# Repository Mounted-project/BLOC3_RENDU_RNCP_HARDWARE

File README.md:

# AugMounted-electronics
Electronic repo for the AugMounted line-up

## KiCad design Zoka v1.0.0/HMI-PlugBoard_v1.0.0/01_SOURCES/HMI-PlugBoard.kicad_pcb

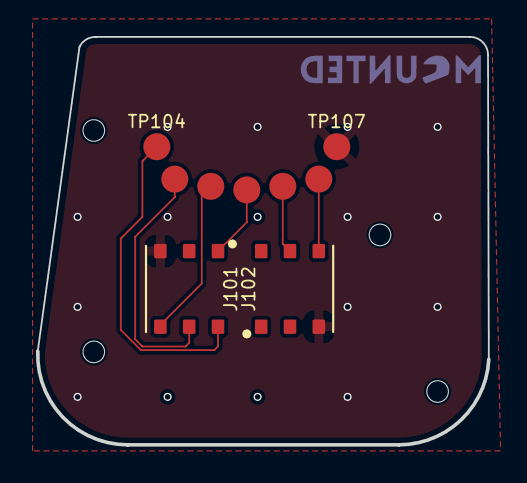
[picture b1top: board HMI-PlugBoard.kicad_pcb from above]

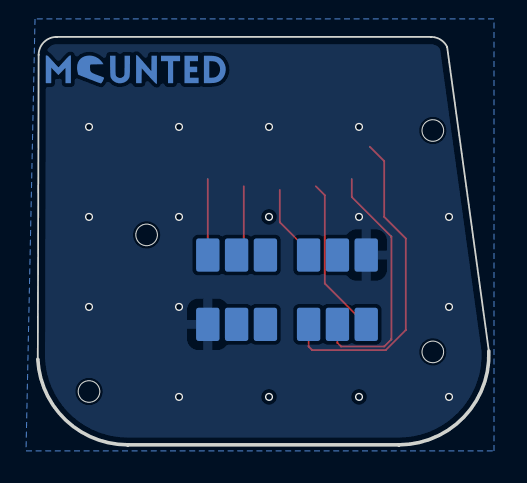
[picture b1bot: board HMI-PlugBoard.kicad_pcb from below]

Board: 2 copper layers, 25.1 x 22.6 mm, 16 parts (3 on the bottom side), 8 nets.

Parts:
H101, H103, H104, H104#2: H_MOUNTING_HOLE_M1; MountingHole_1.2mm_M1
J101, J102: J_0788641001; J_788641001
J101#2, J102#2: J_0788641001_PAD; J_788641001_PAD
LOGO101: mounted_logo
TP101, TP102, TP103, TP104, TP105, TP106, TP107: TESTPOINT_1.5MM

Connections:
/BUTTON1_HMI_BOARD: J101.5, J101#2.5, TP106.1
/BUTTON2_HMI_BOARD: J101.4, J101#2.4, TP105.1
/ENCODER_A_HMI_BOARD: J102.5, J102#2.5, TP101.1
/ENCODER_B_HMI_BOARD: J102.4, J102#2.4, TP102.1
/ENCODER_S1_HMI_BOARD: J102.1, J102#2.1, TP103.1
/ENCODER_S2_HMI_BOARD: J102.6, J102#2.6, TP104.1
GND: J101.3, J101#2.3, J102.3, J102#2.3, TP107.1
VBUS: J102.2, J102#2.2

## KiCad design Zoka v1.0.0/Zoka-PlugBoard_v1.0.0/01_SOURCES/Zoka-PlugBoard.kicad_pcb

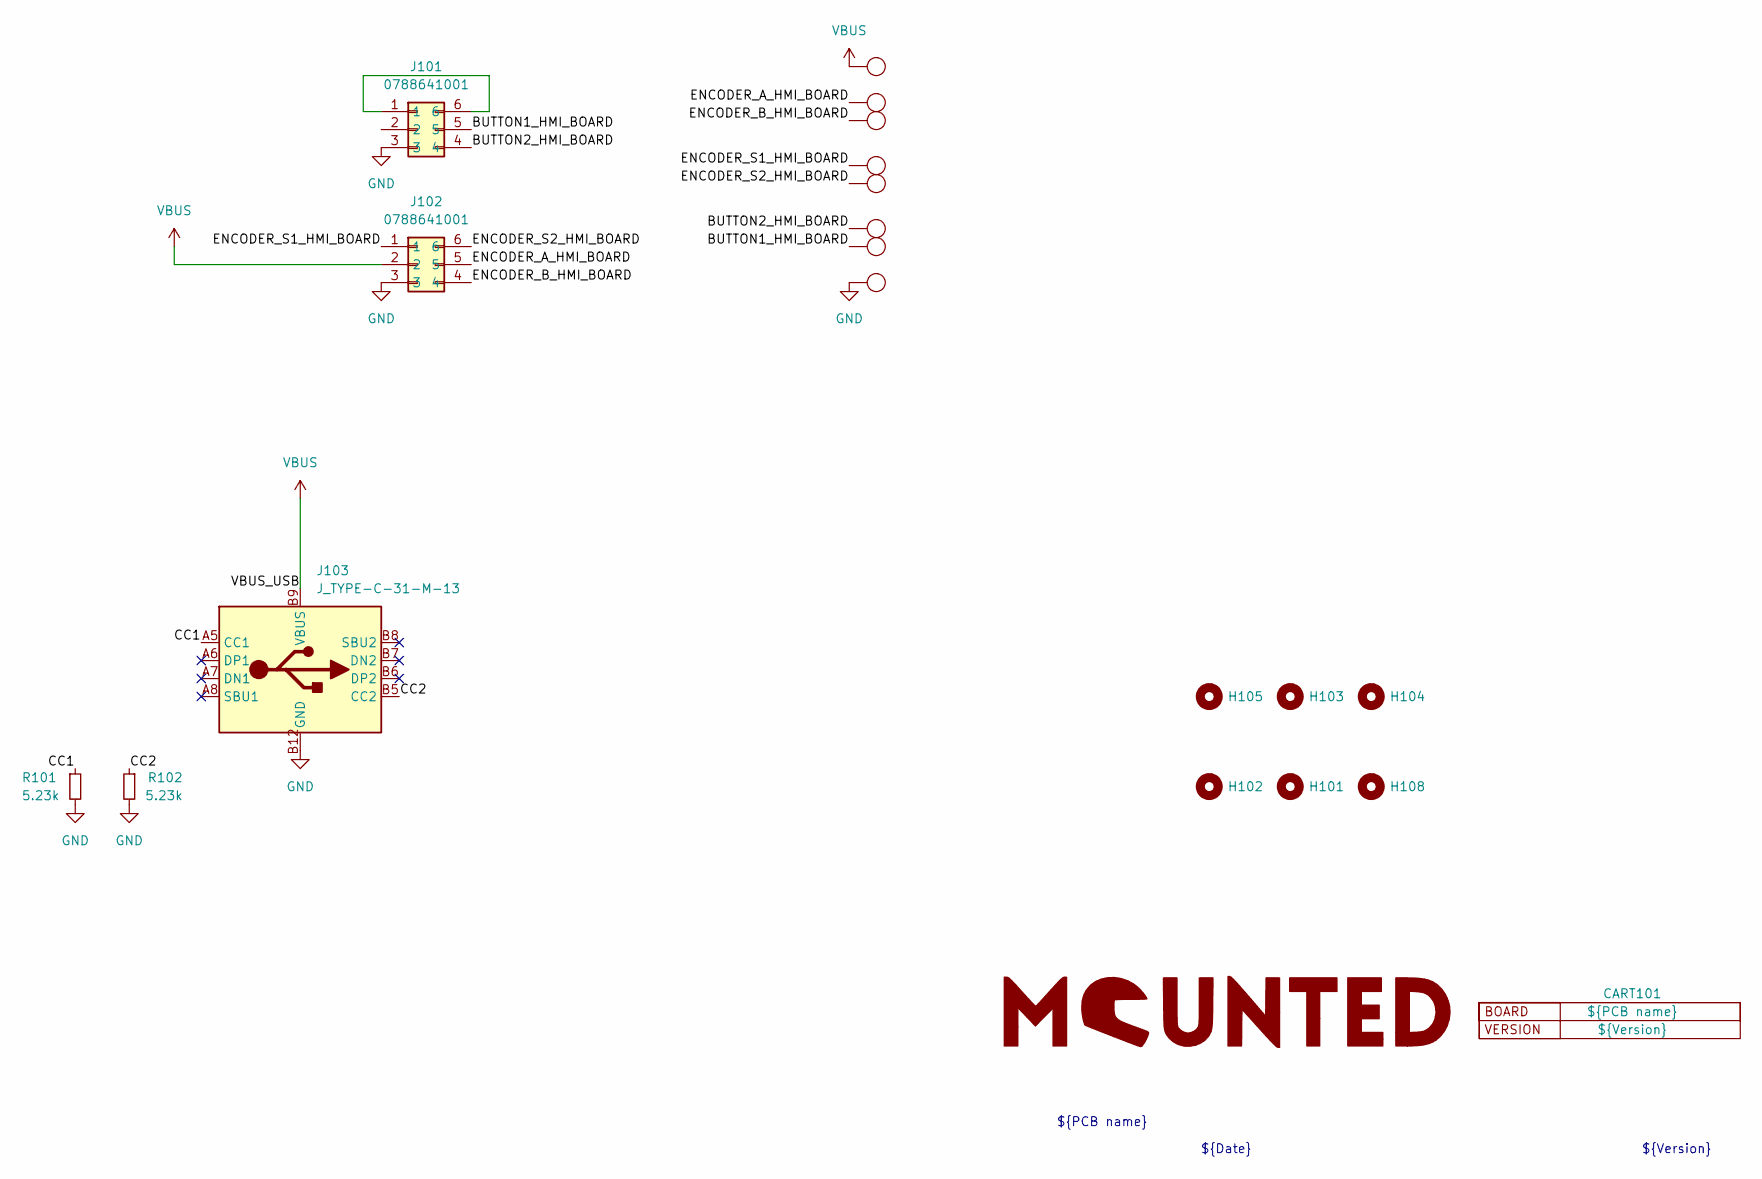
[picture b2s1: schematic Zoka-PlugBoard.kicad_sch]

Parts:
CART101: Cartouche_IO
H101, H102, H103, H104, H105, H108: H_MOUNTING_HOLE_M1; MountingHole_1.2mm_M1
J101, J102: J_0788641001; J_788641001; MPN 0788641001
J103: J_TYPE-C-31-M-13; MPN TYPE-C-31-M-13
LOGO101: mounted_logo
R101, R102: R_0603_5.23k_1%_0.1W; R_0402_1005Metric; Tolerance 1%
TP101, TP102, TP103, TP104, TP105, TP106, TP107, TP108: TESTPOINT_1.5MM

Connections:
/BUTTON1_HMI_BOARD: J101.5, TP106.1
/BUTTON2_HMI_BOARD: J101.4, TP105.1
/CC1: J103.A5 (CC1), R101.1
/CC2: J103.B5 (CC2), R102.1
/ENCODER_A_HMI_BOARD: J102.5, TP101.1
/ENCODER_B_HMI_BOARD: J102.4, TP102.1
/ENCODER_S1_HMI_BOARD: J102.1, TP103.1
/ENCODER_S2_HMI_BOARD: J102.6, TP104.1
GND: J101.3, J102.3, J103.A1 (GND), J103.A12 (GND), J103.B1 (GND), J103.B12 (GND), J103.GND, R101.2, R102.2, TP107.1
unnamed: J101.1, J101.6
VBUS: J102.2, J103.A4 (VBUS), J103.A9 (VBUS), J103.B4 (VBUS), J103.B9 (VBUS), TP108.1

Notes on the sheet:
${PCB name}
${Date}
${Version}

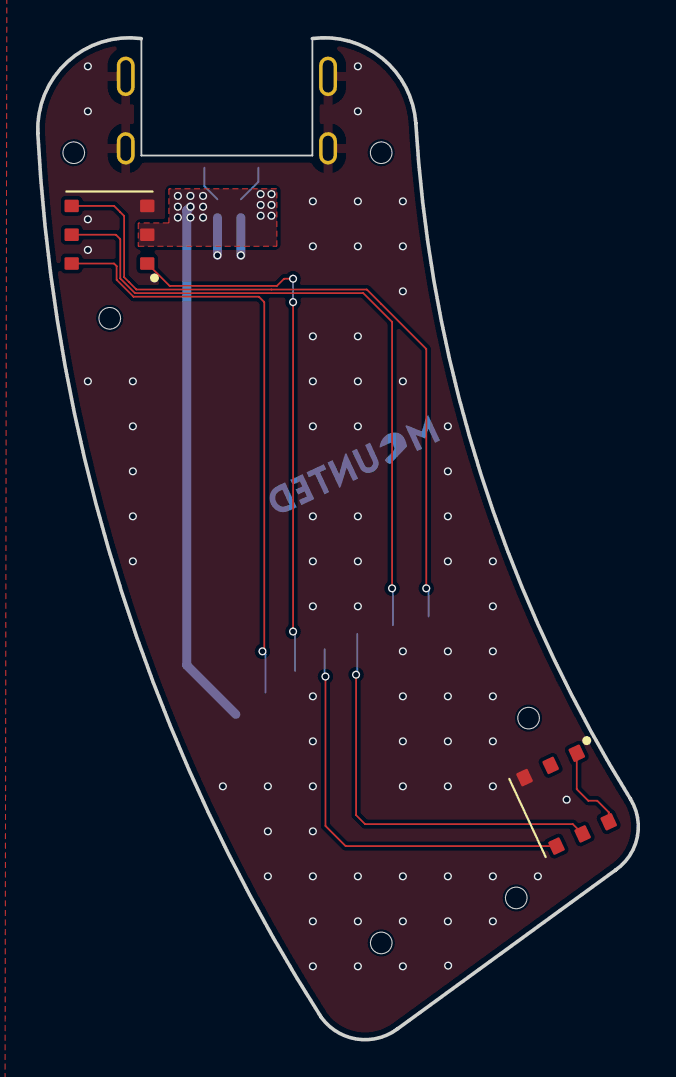
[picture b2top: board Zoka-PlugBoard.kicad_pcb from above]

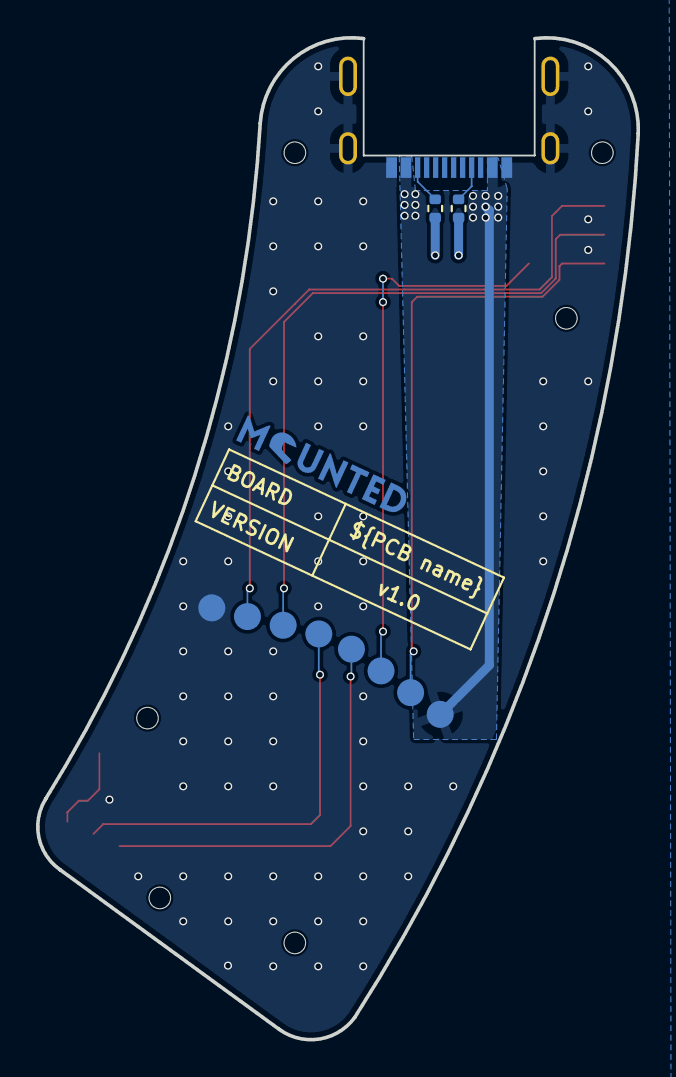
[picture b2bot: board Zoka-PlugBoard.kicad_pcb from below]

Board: 4 copper layers, 33.4 x 55.7 mm, 21 parts (13 on the bottom side), 11 nets.

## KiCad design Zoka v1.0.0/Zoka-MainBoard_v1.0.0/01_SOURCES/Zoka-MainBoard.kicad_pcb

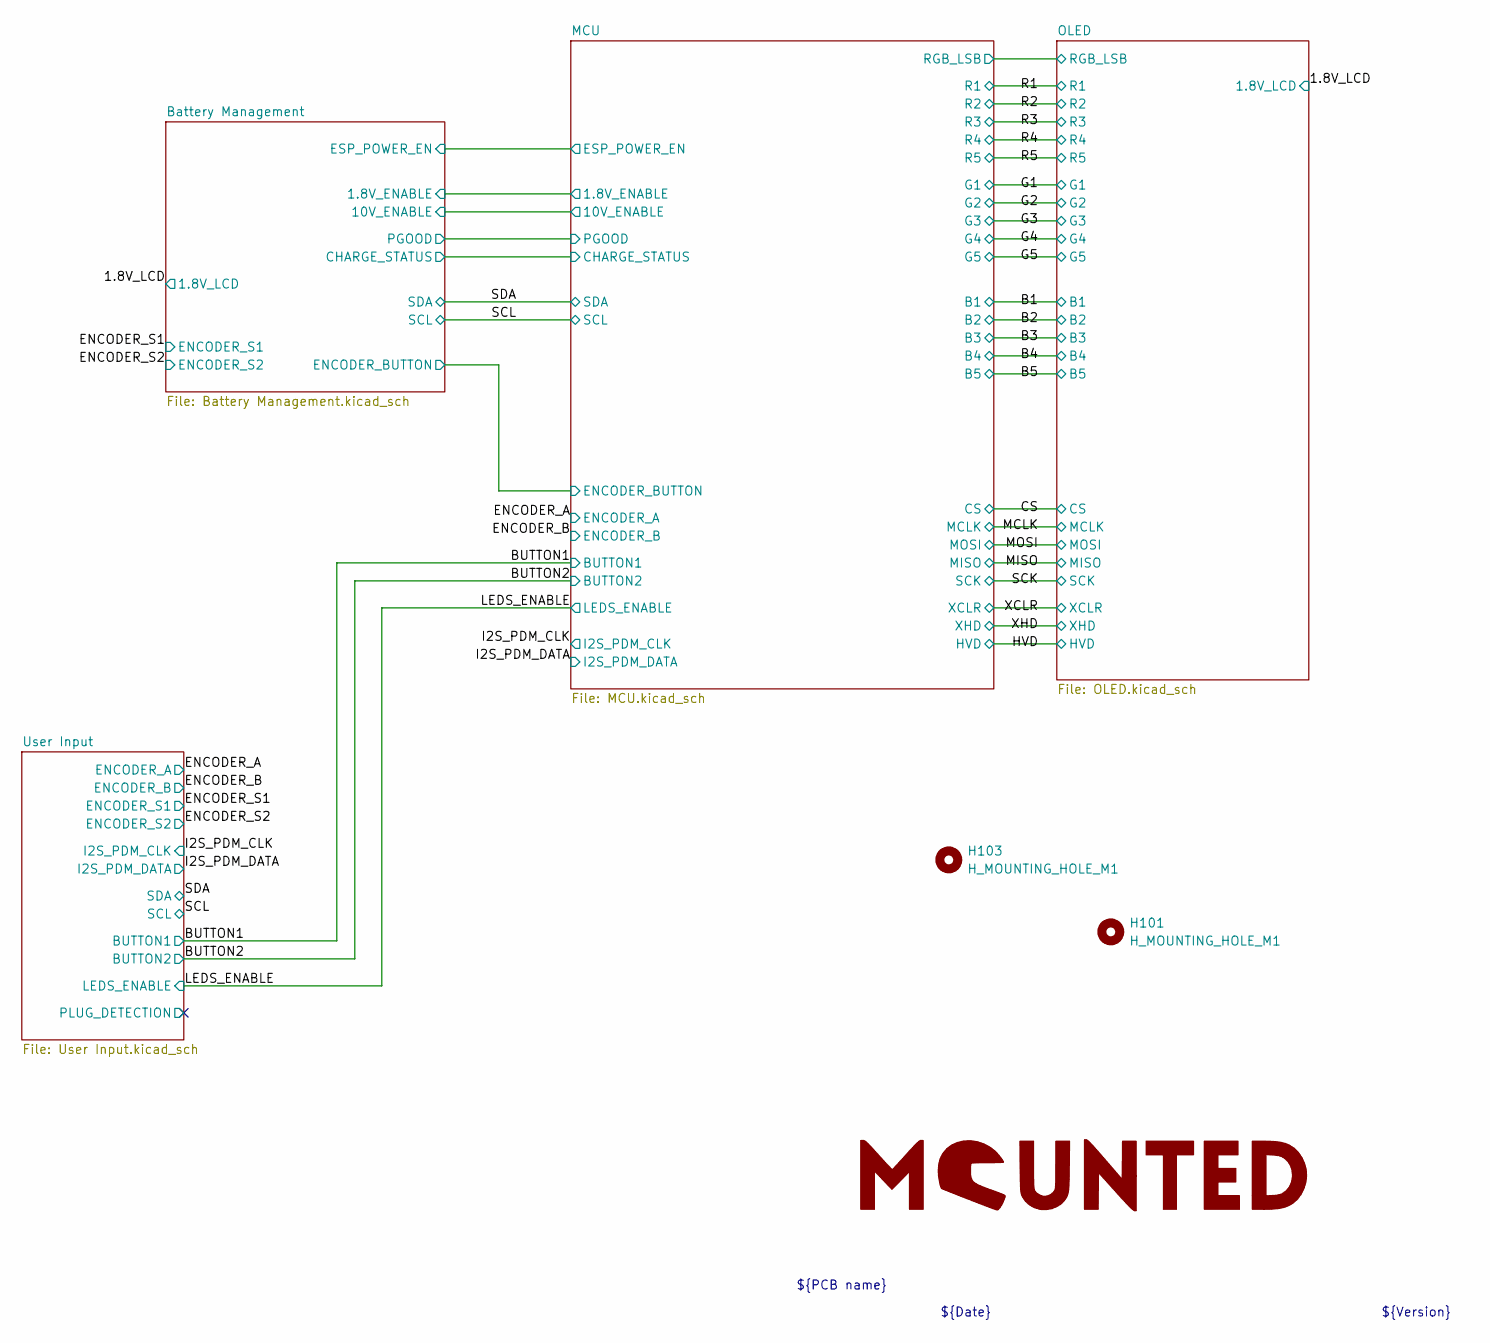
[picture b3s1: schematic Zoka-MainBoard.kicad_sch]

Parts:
H101, H103: H_MOUNTING_HOLE_M1; MountingHole_1.2mm_M1
LOGO101: mounted_logo

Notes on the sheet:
${PCB name}
${Date}
${Version}

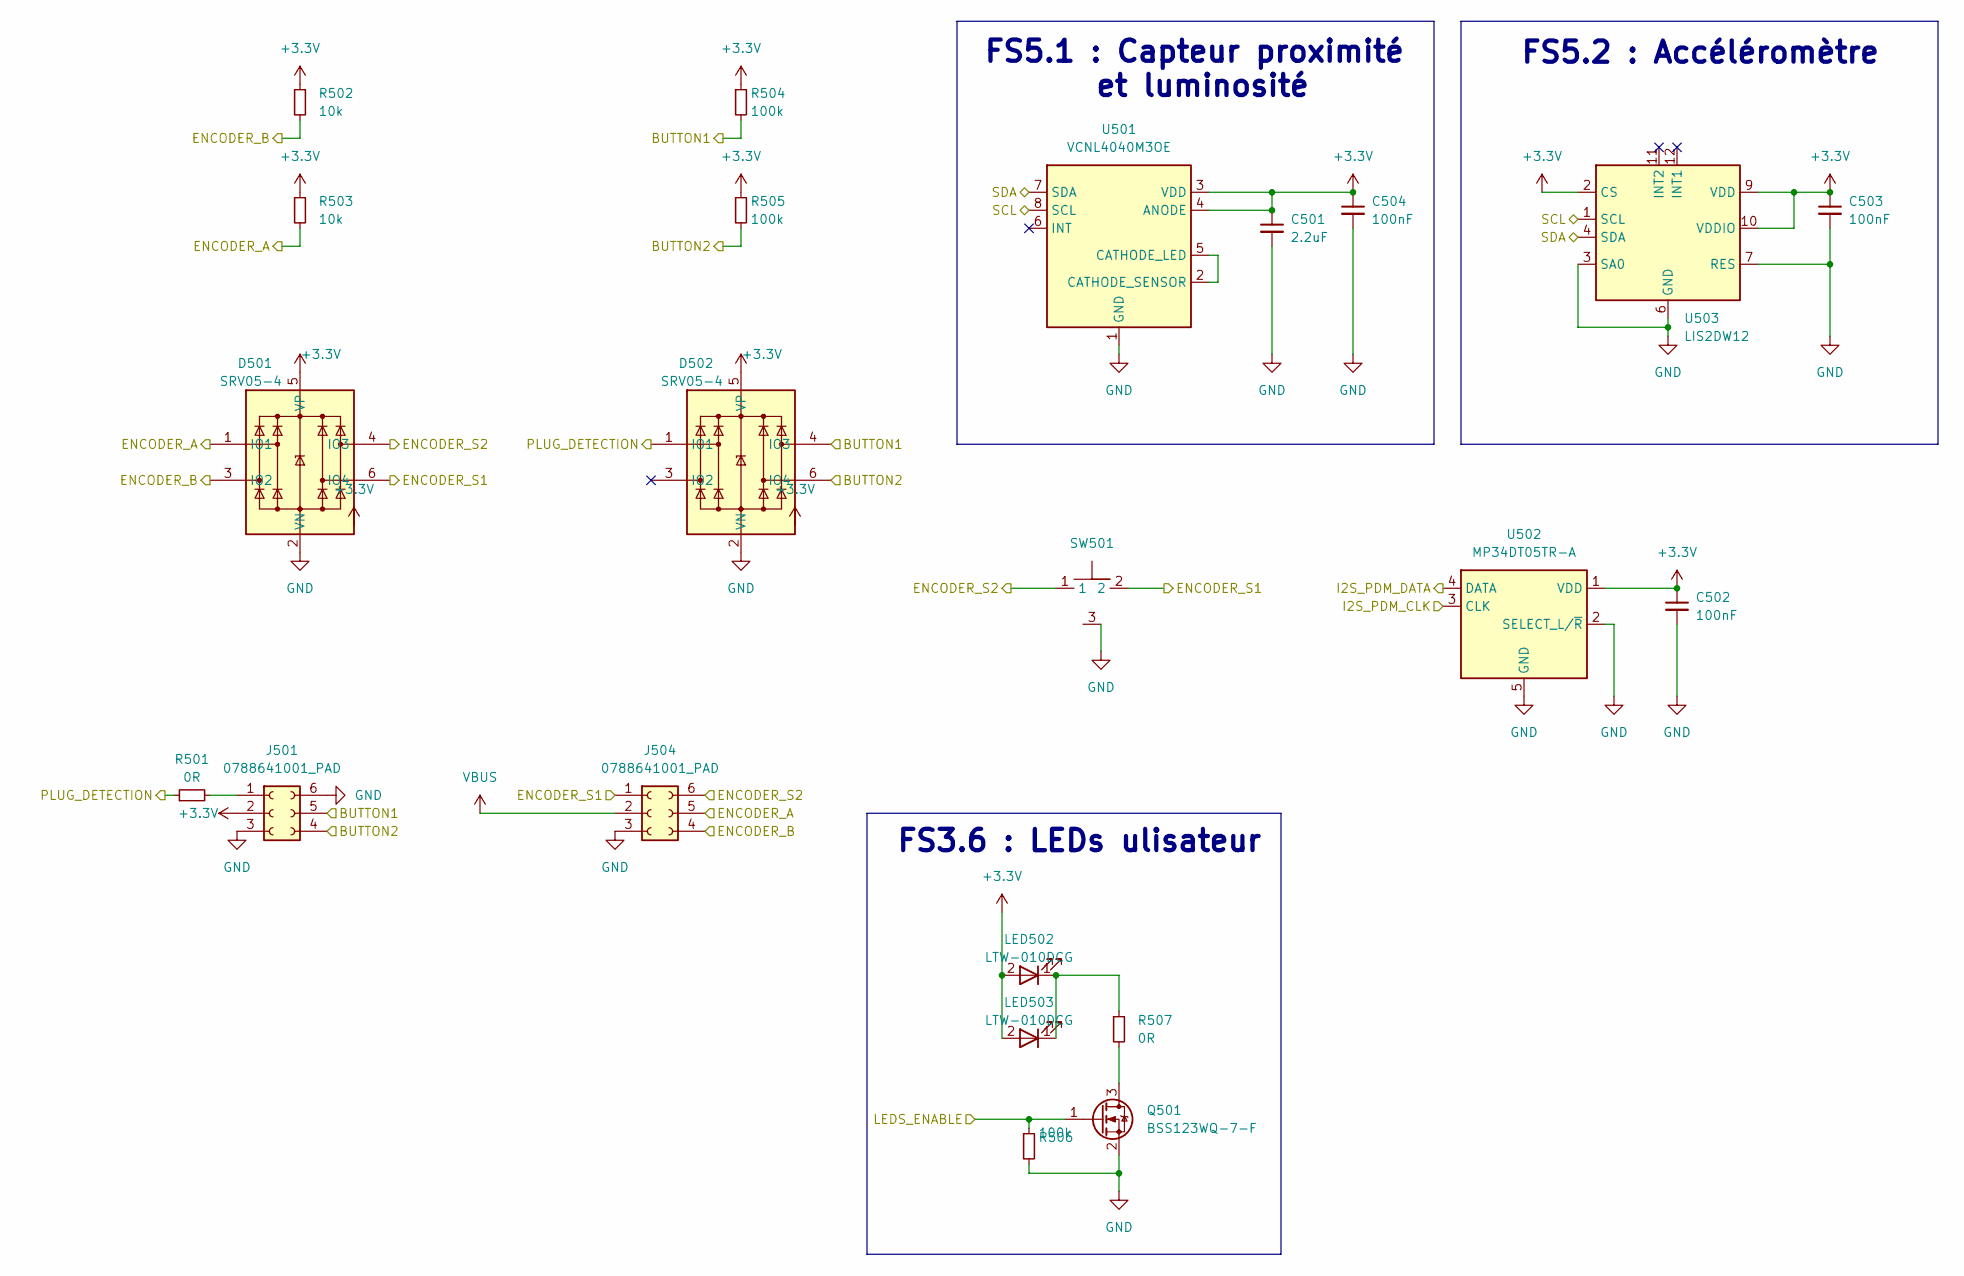
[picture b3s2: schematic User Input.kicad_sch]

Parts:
C501: C_0603_2.2uF_10V_X7R_10%; C_0603_1608Metric; Voltage 10V; Tolerance 10%
C502, C503, C504: C_0603_100nF_100V_X7R_10%; C_0402_1005Metric; Voltage 50V; Tolerance 10%
D501, D502: D_SRV05-4; SOT-23-6_TECH_PUBLIC; MPN SRV05-4
J501, J504: J_0788641001_PAD; J_788641001_PAD; MPN 0788641001
LED502, LED503: LED_LTW-010DCG; MPN LTW-010DCG
Q501: Q_BSS123WQ-7-F; SOT-323_SC-70_DIODES_INC; MPN BSS123WQ-7-F
R501, R507: R_0402_0R_1%_0.06W; R_0402_1005Metric; Tolerance 1%
R502, R503: R_0603_10k_1%_0.1W; R_0402_1005Metric; Tolerance 1%
R504, R505, R506: R_0402_100k_1%_0.06W; R_0402_1005Metric; Tolerance 1%
SW501: SW_SKRTLAE010; MPN SKRTLAE010
U501: U_VCNL4040M3OE; VCNL4040_4X2X1.1_VISHAY; MPN VCNL4040M3OE
U502: MP34DT05TR-A; U_MP34DT05TR-A; MPN MP34DT05TR-A
U503: LIS2DW12; LGA-12_2x2mm_P0.5mm; MPN LIS2DW12

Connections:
+3.3V: C501.1, C502.1, C503.1, C504.1, D501.5 (VP), D502.5 (VP), J501.2, LED502.2 (A), LED503.2 (A), R502.1, R503.1, R504.1, R505.1, U501.3 (VDD), U501.4 (ANODE), U502.1 (VDD), U503.2 (CS), U503.9 (VDD), U503.10 (VDDIO); also elsewhere on the board
/BUTTON1: D502.4 (IO3), J501.5, R504.2; also elsewhere on the board
/BUTTON2: D502.6 (IO4), J501.4, R505.2; also elsewhere on the board
/ENCODER_A: D501.1 (IO1), J504.5, R503.2; also elsewhere on the board
/ENCODER_B: D501.3 (IO2), J504.4, R502.2; also elsewhere on the board
/ENCODER_S1: D501.6 (IO4), J504.1, SW501.2; also elsewhere on the board
/ENCODER_S2: D501.4 (IO3), J504.6, SW501.1; also elsewhere on the board
/I2S_PDM_CLK: U502.3 (CLK); also elsewhere on the board
/I2S_PDM_DATA: U502.4 (DATA); also elsewhere on the board
/LEDS_ENABLE: Q501.1 (G), R506.1; also elsewhere on the board
/SCL: U501.8 (SCL), U503.1 (SCL); also elsewhere on the board
/SDA: U501.7 (SDA), U503.4 (SDA); also elsewhere on the board
/User Input/PLUG_DETECTION: D502.1 (IO1), R501.1
GND: C501.2, C502.2, C503.2, C504.2, D501.2 (VN), D502.2 (VN), J501.3, J501.6, J504.3, Q501.2 (S), R506.2, SW501.3, U501.1 (GND), U502.2 (SELECT_L/~R), U502.5 (GND), U503.3 (SA0), U503.6 (GND), U503.7 (RES), U503.8 (GND); also elsewhere on the board
unnamed: J501.1, R501.2
unnamed: LED502.1 (K), LED503.1 (K), R507.1
unnamed: Q501.3 (D), R507.2
unnamed: U501.2 (CATHODE_SENSOR), U501.5 (CATHODE_LED)
VBUS: J504.2; also elsewhere on the board

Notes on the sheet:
FS5.2 : Accéléromètre
FS5.1 : Capteur proximité et luminosité
FS3.6 : LEDs ulisateur

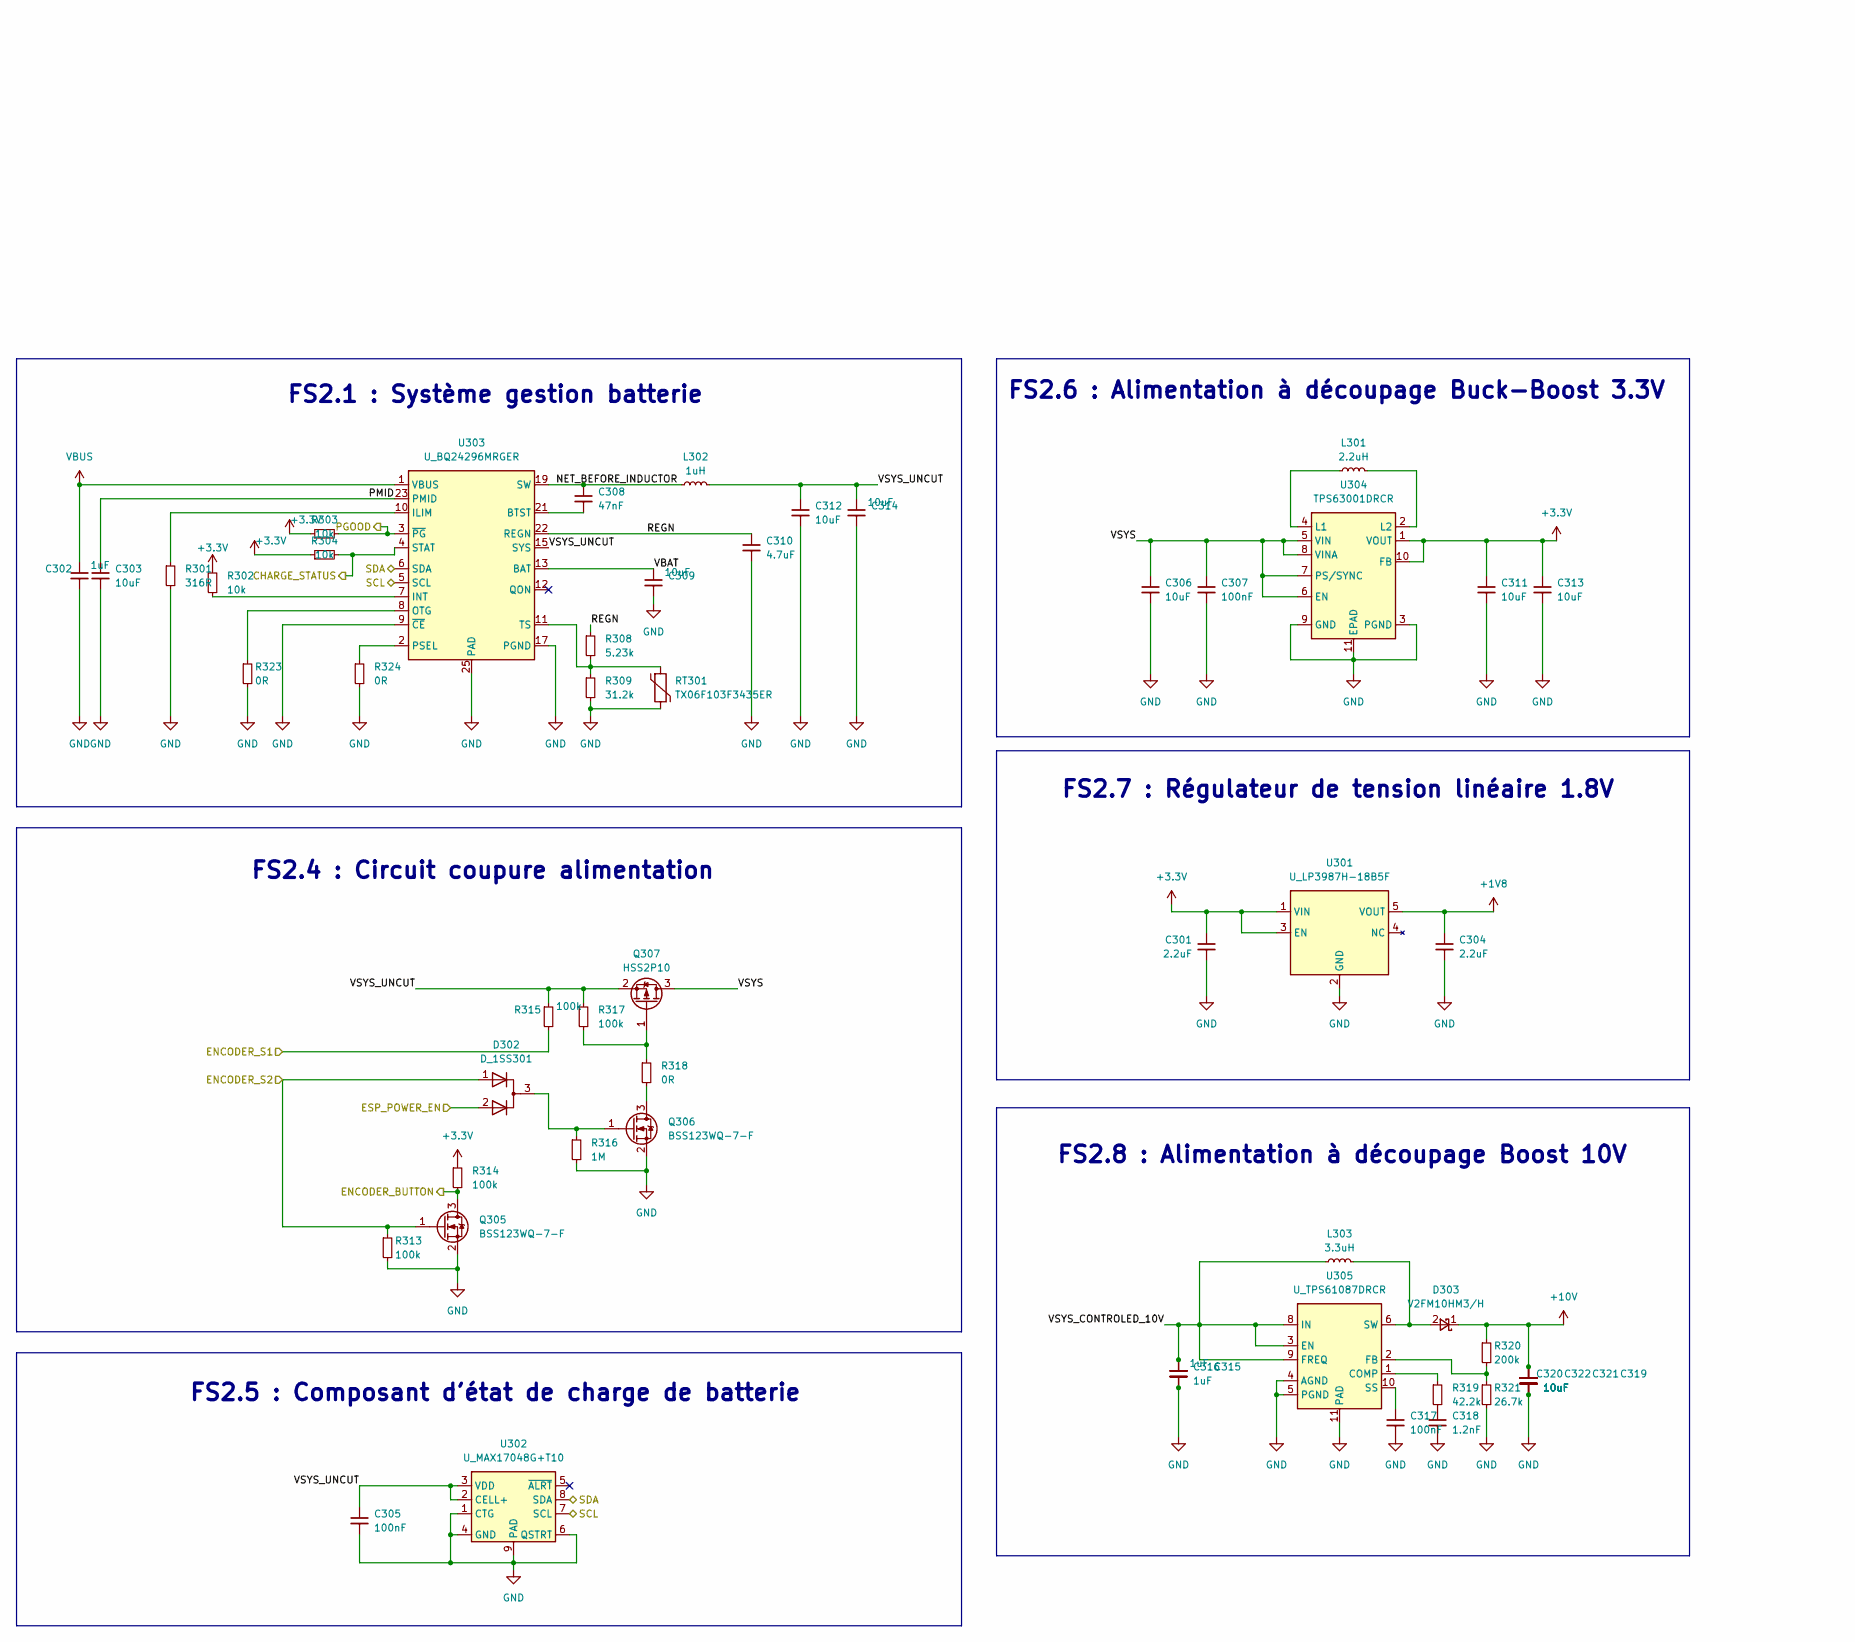
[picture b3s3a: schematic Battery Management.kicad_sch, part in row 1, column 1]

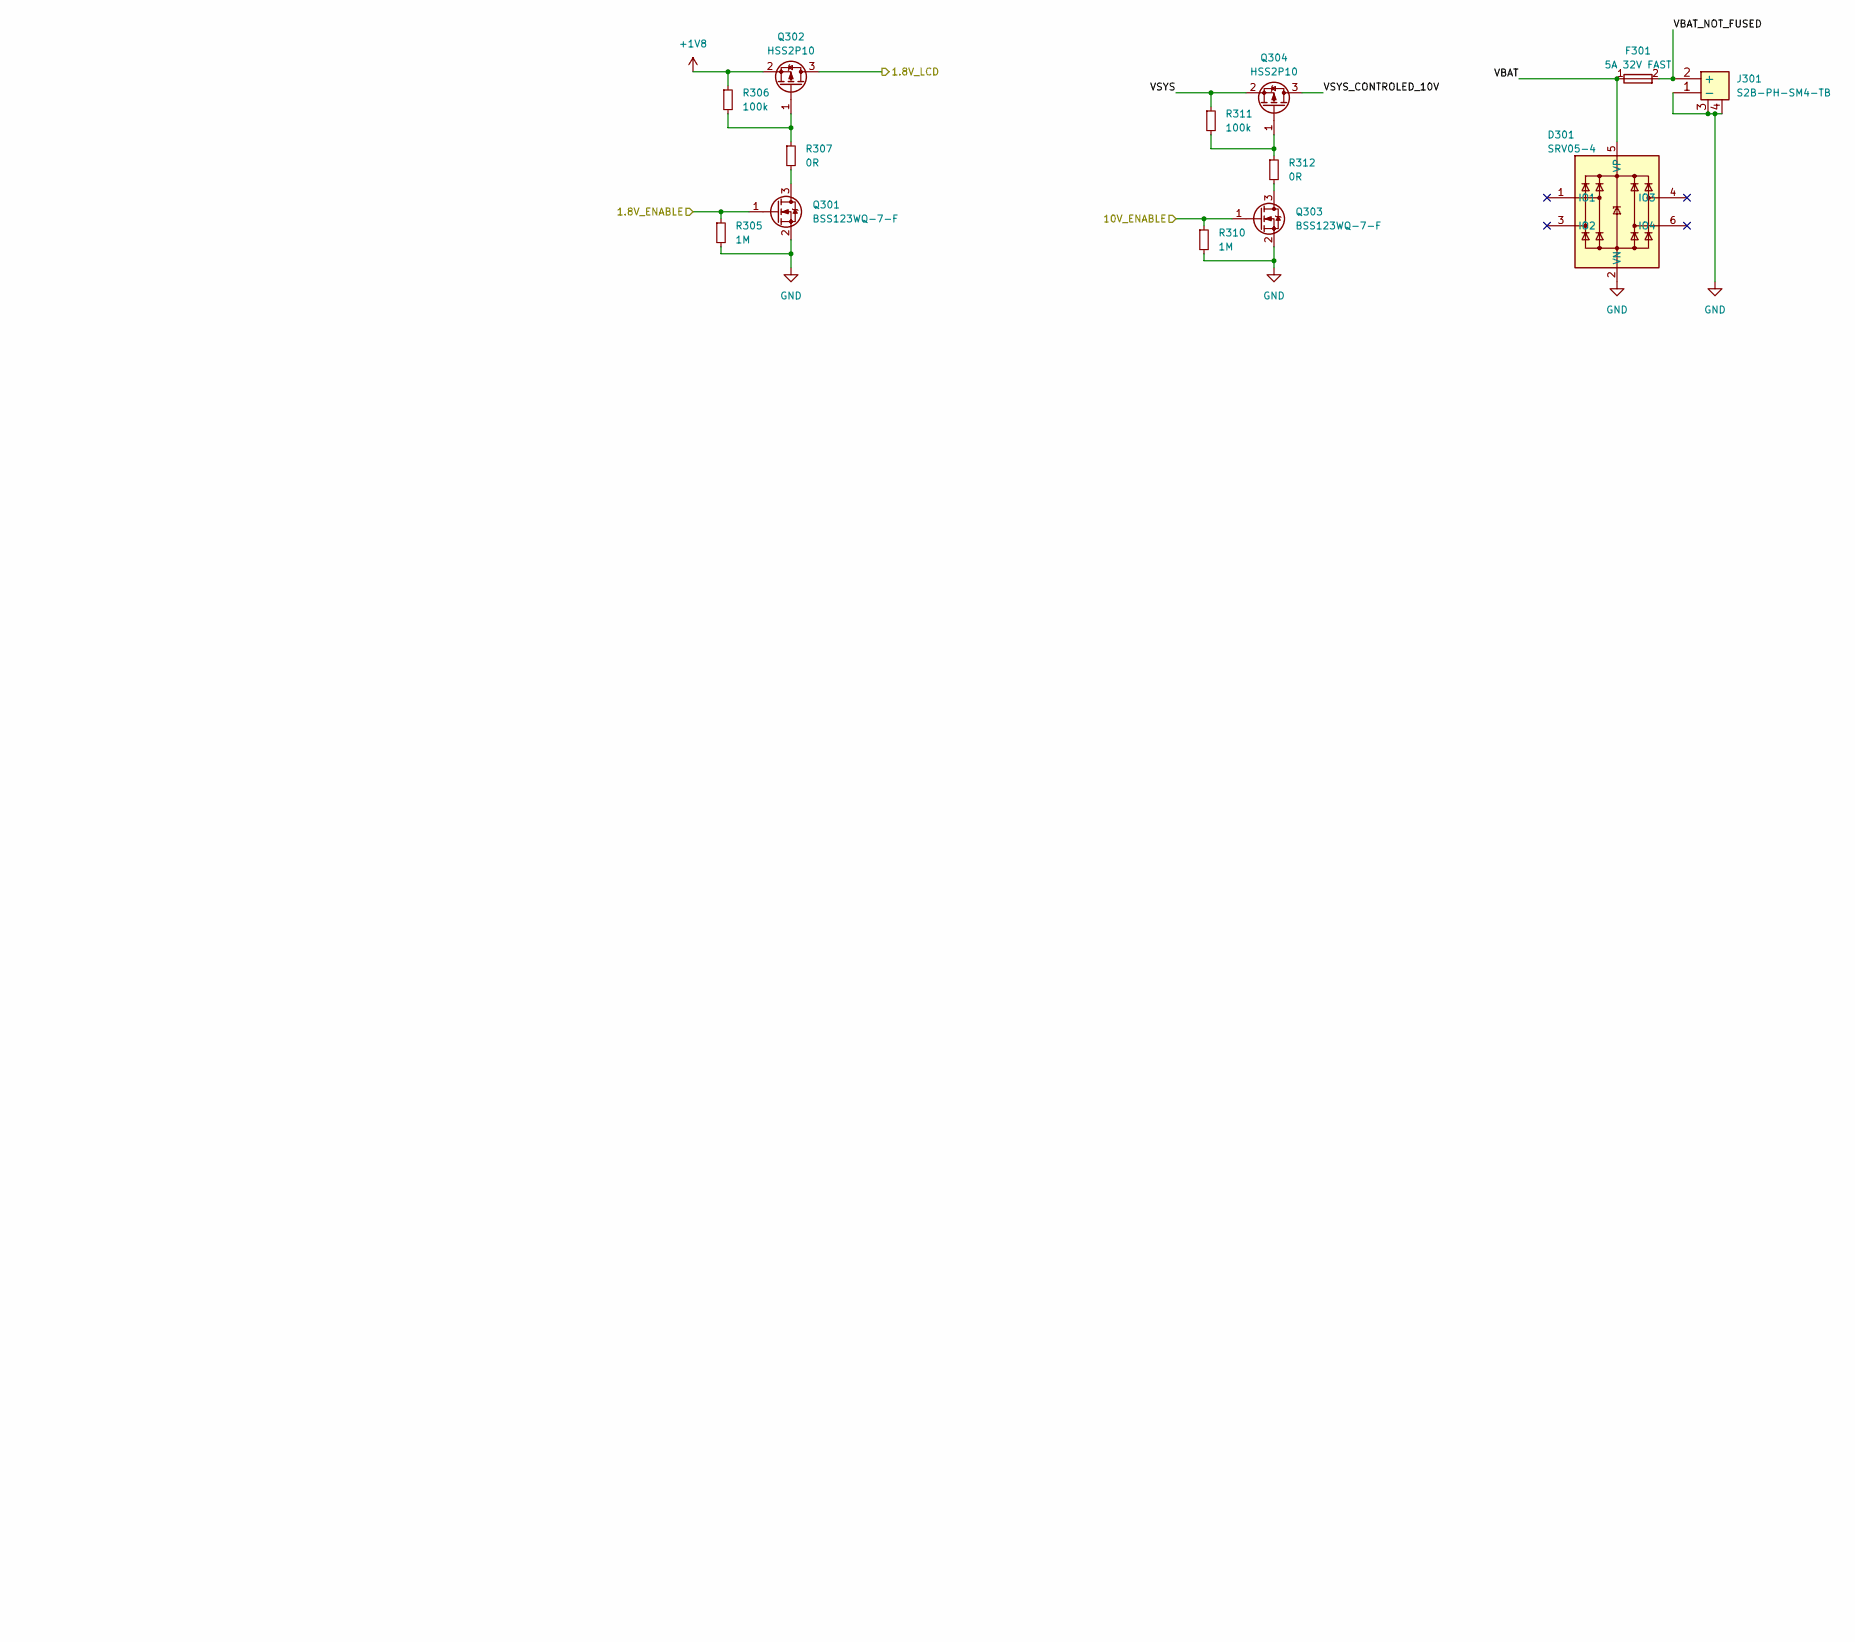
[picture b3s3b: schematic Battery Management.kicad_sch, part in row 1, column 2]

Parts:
C301, C304: C_0805_2.2uF_25V_X7R_20%; C_0805_1608Metric; Voltage 25V; Tolerance 20%
C302, C315, C316: C_0402_1uF_10V_X7R_10%; C_0402_1005Metric; Voltage 10V; Tolerance 10%
C303, C306, C309, C311, C312, C313, C314: C_0805_10uF_10V_X7R_10%; C_0805_1608Metric; Voltage 25V; Tolerance 10%
C305, C307, C317: C_0603_100nF_100V_X7R_10%; C_0402_1005Metric; Voltage 50V; Tolerance 10%
C308: C_0402_47nF_50V_X7R_10%; C_0402_1005Metric; Voltage 50V; Tolerance 10%
C310: C_0603_4.7uF_16V_X7R_10%; C_0603_1608Metric; Voltage 16V; Tolerance 10%
C318: C_0402_1.2nF_50V_X7R_10%; C_0402_1005Metric; Voltage 50V; Tolerance 10%
C319, C320, C321, C322: C_1206_10uF_25V_X7R_10%; C_0805_1608Metric; Voltage 25V; Tolerance 10%; PartStatus ___PartStatus
D301: D_SRV05-4; SOT-23-6_TECH_PUBLIC; MPN SRV05-4
D302: D_1SS301; SOT-23_TOSHIBA; MPN 1SS301,LF
D303: D_V2FM10HM3/H; D_SMF_VISHAY; MPN V2FM10HM3/H
F301: F_MFU0603FF05000P100; R_0603_1608Metric; MPN MFU0603FF05000P100
J301: J_JST_S2B-PH-SM4-TB; MPN S2B-PH-SM4-TB
L301: L_FNR3015S2R2MT; Tolerance 20%; MPN FNR3015S2R2MT
L302: L_TFM252012ALMA1R0MTAA; TFM252012ALMA1R0MTAA; MPN TFM252012ALMA1R0MTAA
L303: L_7447789003; Tolerance 20%; MPN 7447789003
Q301, Q303, Q305, Q306: Q_BSS123WQ-7-F; SOT-323_SC-70_DIODES_INC; MPN BSS123WQ-7-F
Q302, Q304, Q307: Q_HSS2P10; SOT-23-3_HUASHUO; MPN HSS2P10
R301: R_0402_316R_1%_0.06W; R_0402_1005Metric; Tolerance 1%
R302, R303, R304: R_0402_10k_1%_0.06W; R_0402_1005Metric; Tolerance 1%
R305, R310, R316: R_0603_1M_1%_0.1W; R_0402_1005Metric; Tolerance 1%
R306, R311, R313, R314, R315, R317: R_0402_100k_1%_0.06W; R_0402_1005Metric; Tolerance 1%
R307, R312, R318, R323, R324: R_0402_0R_1%_0.06W; R_0402_1005Metric; Tolerance 1%
R308: R_0402_5.23k_1%_0.06W; R_0402_1005Metric; Tolerance 1%
R309: R_0603_31.2k_0.5%_0.1W; R_0603_1608Metric; Tolerance 0.5%
R319: R_0402_42.2k_1%_0.06W; R_0402_1005Metric; Tolerance 1%
R320: R_0402_200k_1%_0.06W; R_0402_1005Metric; Tolerance 1%; PartStatus ___PartStatus
R321: R_0402_26.7k_1%_0.06W; R_0402_1005Metric; Tolerance 1%; PartStatus ___PartStatus
RT301: RT_TX06F103F3435ER; NTCG16_XXX_TDK; Tolerance 1%; MPN TX06F103F3435ER
U301: U_LP3987H-18B5F; SOT-23-5_LOW_POWER; MPN LP3987H-18B5F
U302: U_MAX17048G+T10; TDFN-8_MAXIM_INTEGRATED; MPN MAX17048G+T10
U303: U_BQ24296MRGER; VQFN-24_TEXAS_INSTRUMENTS; MPN BQ24296MRGER
U304: U_TPS63001DRCR; PVSON-N10_TEXAS_INSTRUMENTS; MPN TPS63001DRCR
U305: U_TPS61087DRCR; PVSON-N10_TEXAS_INSTRUMENTS; MPN TPS61087DRCR

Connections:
+1V8: C304.1, Q302.2 (S), R306.1, U301.5 (VOUT); also elsewhere on the board
+3.3V: C301.1, C311.1, C313.1, R302.1, R303.1, R304.1, R314.1, U301.1 (VIN), U301.3 (EN), U304.1 (VOUT), U304.10 (FB); also elsewhere on the board
+10V: C319.1, C320.1, C321.1, C322.1, D303.1 (K), R320.1; also elsewhere on the board
/1.8V_LCD: Q302.3 (D); also elsewhere on the board
/Battery Management/1.8V_ENABLE: Q301.1 (G), R305.1; also elsewhere on the board
/Battery Management/10V_ENABLE: Q303.1 (G), R310.1; also elsewhere on the board
/Battery Management/CHARGE_STATUS: R304.2, U303.4 (STAT); also elsewhere on the board
/Battery Management/ENCODER_BUTTON: Q305.3 (D), R314.2; also elsewhere on the board
/Battery Management/ESP_POWER_EN: D302.2 (A2); also elsewhere on the board
/Battery Management/NET_BEFORE_INDUCTOR: C308.1, L302.1, U303.19 (SW), U303.20 (SW)
/Battery Management/PGOOD: R303.2, U303.3 (~PG); also elsewhere on the board
/Battery Management/PMID: C303.1, U303.23 (PMID)
/Battery Management/VBAT: C309.1, D301.5 (VP), F301.1, U303.13 (BAT), U303.14 (BAT)
/Battery Management/VBAT_NOT_FUSED: F301.2, J301.2 (+)
/Battery Management/VSYS: C306.1, C307.1, Q304.2 (S), Q307.3 (D), R311.1, U304.5 (VIN), U304.6 (EN), U304.7 (PS/SYNC), U304.8 (VINA)
/Battery Management/VSYS_CONTROLED_10V: C315.1, C316.1, L303.1, Q304.3 (D), U305.3 (EN), U305.8 (IN), U305.9 (FREQ)
/Battery Management/VSYS_UNCUT: C305.1, C312.1, C314.1, L302.2, Q307.2 (S), R315.1, R317.1, U302.2 (CELL+), U302.3 (VDD), U303.15 (SYS), U303.16 (SYS)
/ENCODER_S1: R315.2; also elsewhere on the board
/ENCODER_S2: D302.1 (A1), Q305.1 (G), R313.1; also elsewhere on the board
/SCL: U302.7 (SCL), U303.5 (SCL); also elsewhere on the board
/SDA: U302.8 (SDA), U303.6 (SDA); also elsewhere on the board
GND: C301.2, C302.2, C303.2, C304.2, C305.2, C306.2, C307.2, C309.2, C310.2, C311.2, C312.2, C313.2, C314.2, C315.2, C316.2, C317.2, C318.2, C319.2, C320.2, C321.2, C322.2, D301.2 (VN), J301.1 (-), J301.3, J301.4, Q301.2 (S), Q303.2 (S), Q305.2 (S), Q306.2 (S), R301.2, R305.2, R309.2, R310.2, R313.2, R316.2, R321.2, R323.2, R324.2, RT301.2, U301.2 (GND), U302.1 (CTG), U302.4 (GND), U302.6 (QSTRT), U302.9 (PAD), U303.9 (~CE), U303.17 (PGND), U303.18 (PGND), U303.25 (PAD), U304.3 (PGND), U304.9 (GND), U304.11 (EPAD), U305.4 (AGND), U305.5 (PGND), U305.11 (PAD); also elsewhere on the board
unnamed: C318.1, R319.2
unnamed: D302.3 (K), Q306.1 (G), R316.1
unnamed: D303.2 (A), L303.2, U305.6 (SW), U305.7 (SW)
unnamed: Q301.3 (D), R307.2
unnamed: Q302.1 (G), R306.2, R307.1
unnamed: Q303.3 (D), R312.2
unnamed: Q304.1 (G), R311.2, R312.1
unnamed: Q306.3 (D), R318.2
unnamed: Q307.1 (G), R317.2, R318.1
unnamed: C308.2, U303.21 (BTST)
unnamed: R301.1, U303.10 (ILIM)
unnamed: R302.2, U303.7 (INT)
unnamed: R323.1, U303.8 (OTG)
unnamed: R324.1, U303.2 (PSEL)
unnamed: L301.1, U304.4 (L1)
unnamed: L301.2, U304.2 (L2)
unnamed: R319.1, U305.1 (COMP)
unnamed: R320.2, R321.1, U305.2 (FB)
unnamed: C317.1, U305.10 (SS)
VBUS: C302.1, U303.1 (VBUS), U303.24 (VBUS); also elsewhere on the board

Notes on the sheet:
FS2.1 : Système gestion batterie
FS2.5 : Composant d'état de charge de batterie
FS2.8 : Alimentation à découpage Boost 10V
FS2.7 : Régulateur de tension linéaire 1.8V
FS2.4 : Circuit coupure alimentation
FS2.6 : Alimentation à découpage Buck-Boost 3.3V
